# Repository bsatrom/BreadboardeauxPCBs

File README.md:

# BreadboardeauxPCBs
PCB Design projects for Breadboardeaux Circuits and projects

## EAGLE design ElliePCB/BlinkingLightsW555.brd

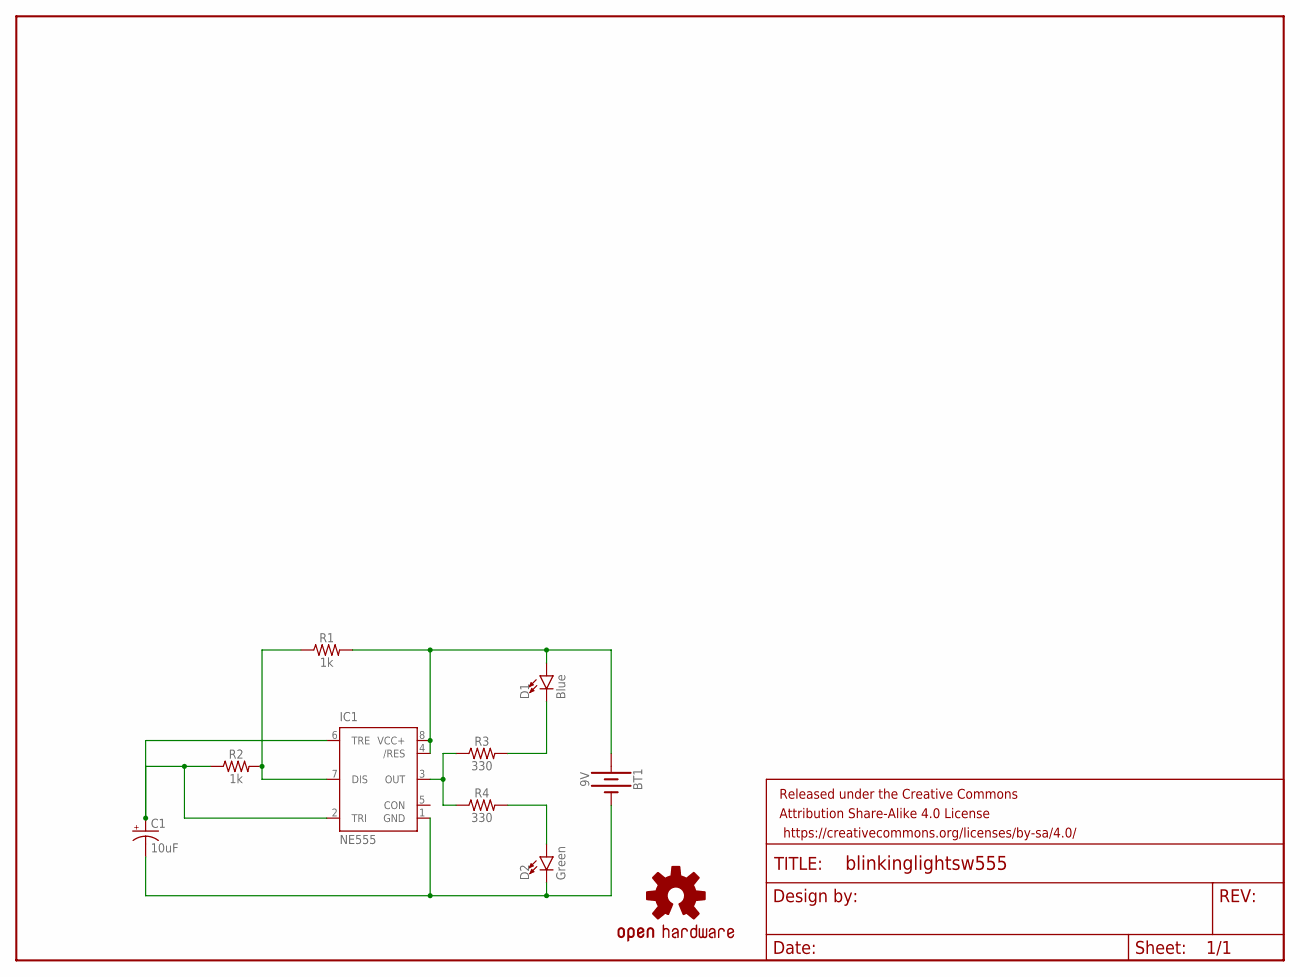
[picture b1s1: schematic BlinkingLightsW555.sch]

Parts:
BT1: 9V; BATTCON_9V
C1: 10uF; CPOL-RADIAL-2.5MM-5MM-KIT
D1: Blue; LED_10MM
D2: Green; LED_10MM
FRAME1: FRAME-LETTERNO_PACKAGE; DUMMY
IC1: NE555; DIL-08
LOGO2: OSHW-LOGOM; OSHW-LOGO-M
R1, R2: 1k; AXIAL-0.3
R3, R4: 330; AXIAL-0.3

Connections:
unnamed: D1.C, R3.P$2 (2)
unnamed: IC1.3 (OUT), R3.P$1 (1), R4.P$1 (1)
unnamed: BT1.+, D1.A, IC1.4 (/RES), IC1.8 (VCC+), R1.P$2 (2)
unnamed: D2.A, R4.P$2 (2)
unnamed: BT1.-, C1.2 (-), D2.C, IC1.1 (GND)
unnamed: IC1.7 (DIS), R1.P$1 (1), R2.P$2 (2)
unnamed: C1.1 (+), IC1.2 (TRI), IC1.6 (TRE), R2.P$1 (1)

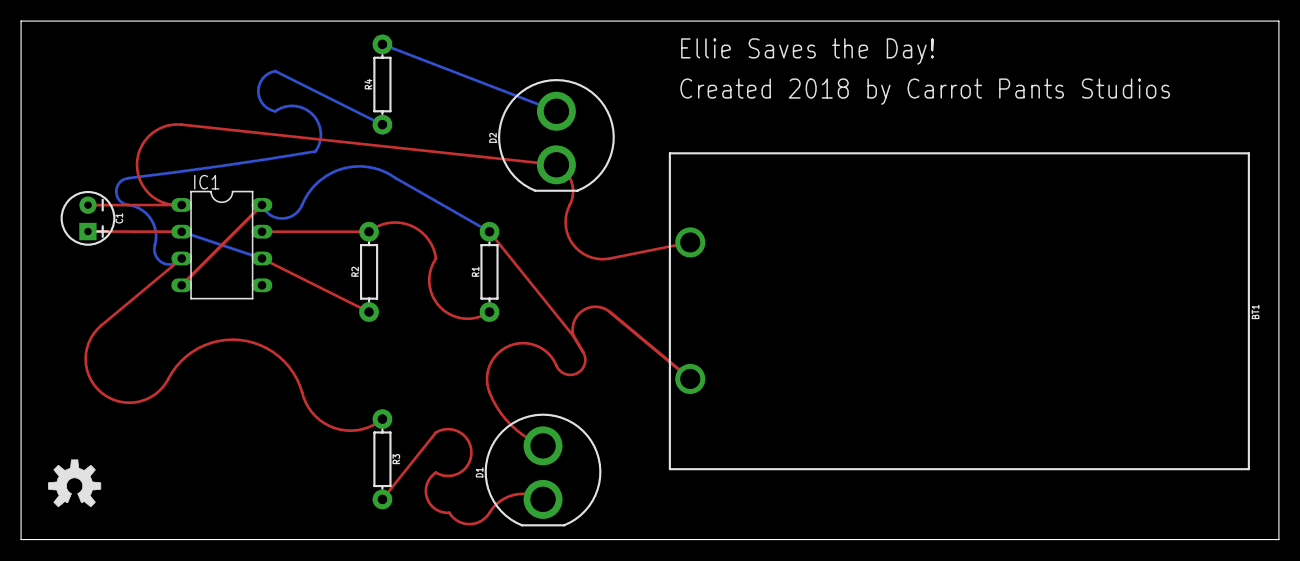
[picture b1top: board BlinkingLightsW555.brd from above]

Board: 2 copper layers, 119.4 x 49.2 mm, 11 parts (0 on the bottom side), 7 nets.

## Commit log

2018-02-23 added PCB design for Ellie Saves the Day
2018-04-13 added KiCad design files

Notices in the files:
parts and their libraries:
SparkFun-Batteries: Licensing: Creative Commons ShareAlike 4.0 International - https://creativecommons.org/licenses/by-sa/4.0
SparkFun-Aesthetics: Released under the Creative Commons Attribution Share-Alike 4.0 License
SparkFun-Aesthetics: https://creativecommons.org/licenses/by-sa/4.0
